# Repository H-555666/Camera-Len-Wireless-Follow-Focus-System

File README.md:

# Camera-Len-Wireless-Follow-Focus-System
***Many documents are not yet complete, the initial version has been released, please wait🌛***

**[简体中文](https://github.com/ZhongWwwHhh/Camera-Len-Wireless-Follow-Focus-System/blob/main/README_ZH_CN.md)**

## Brief Instructions for Use
If you are an enthusiast and only want to make and use it personally, check this document: [Brief instructions for use](https://github.com/ZhongWwwHhh/Camera-Len-Wireless-Follow-Focus-System/blob/main/Documentation/Quickstart.md)

## Developer
This project always welcomes your guidance and help!!!  
This project was designed exclusively for Raspberry Pi Pico.
If you want to use it on other micropython-capable microcontrollers(such as a more powerful Arduino or pyboard), there's another [code explanation](https://github.com/ZhongWwwHhh/Camera-Len-Wireless-Follow-Focus-System/blob/main/Documentation/Codeinterpretation.md) will make this process easier

## Introduction to Project
The project currently implements a rocker potentiometer (the one on an aeromodelling remote control) to remotely and wirelessly control a stepper motor.  
It only requires two Raspberry Pi Pico, a ULN2003 and its driven stepper motor, and a pair of wireless transceiver modules, aiming to achieve the same functional equipment as an expensive commercial wireless follower.  
***In the future, it will gradually increase to be able to control the version of three motors, and add more powerful functions such as A-B point limit, see [Development Log](https://github.com/ZhongWwwHhh/Camera-Len-Wireless-Follow-Focus-System/blob/main/Documentation/Updatelog.md)***  
Receiver and transmitter use the same modular hardware design (PCB), Transmitter-receiver conversion can be achieved by simply brushing different programs  
All software will use micropython for easy modification and application, and all hardware will be designed with Kicad

## Development and business use
Please note: **All software and hardware in this repository follow GPL3. 0 (GNU General Public License v3.0)**  
You can **get usage modifications**, but everything will continue to follow GPL3. 0 Protocol  
If you make it a commodity, then you **have to** let **anyone** know **its nature and get the source code / source design file**  
See for more information [original GPL3.0 file](https://github.com/ZhongWwwHhh/Camera-Len-Wireless-Follow-Focus-System/blob/main/LICENSE)

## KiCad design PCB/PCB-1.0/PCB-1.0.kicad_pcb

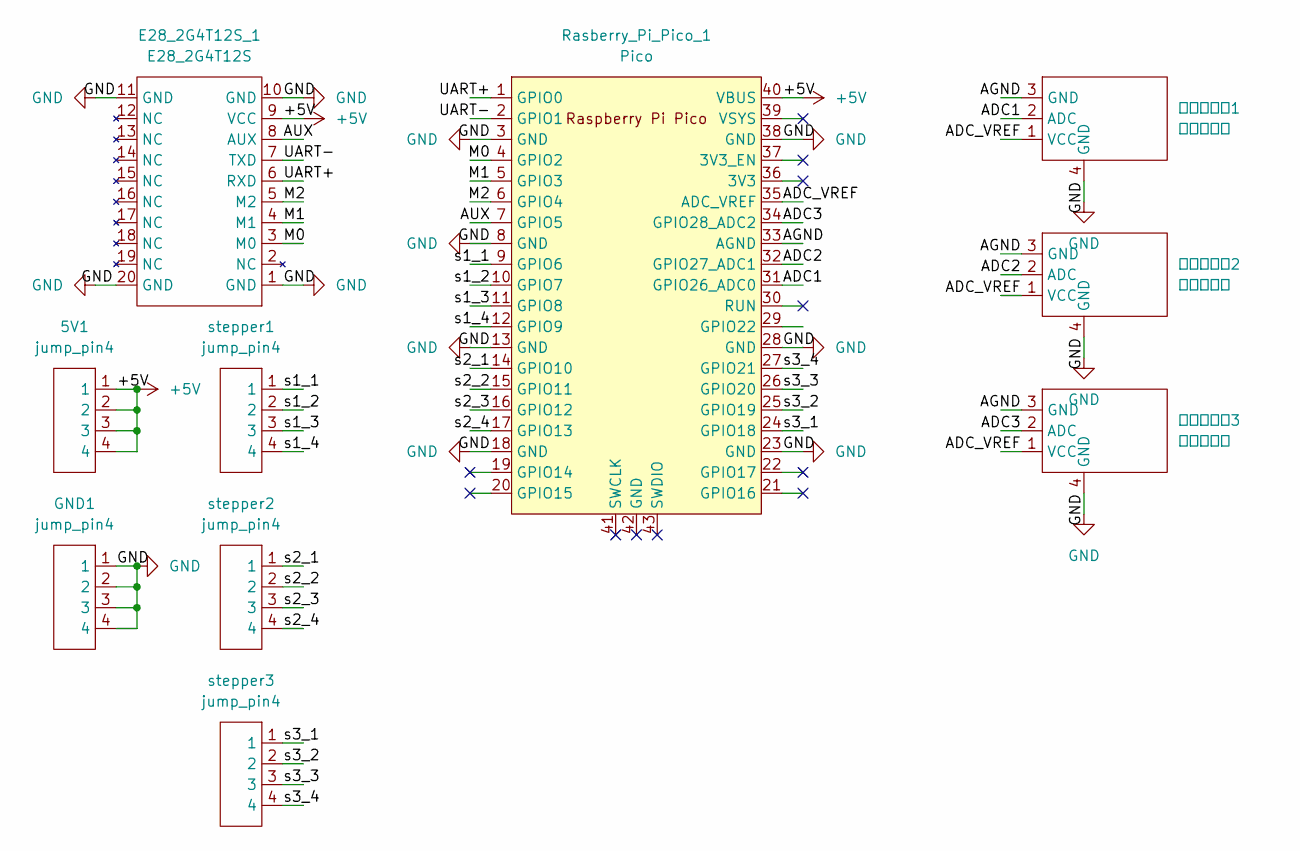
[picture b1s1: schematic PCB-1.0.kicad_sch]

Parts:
5V1: jump_pin4; SIP-4
E28_2G4T12S_1: E28_2G4T12S
GND1: jump_pin4; SIP-4
Rasberry_Pi_Pico_1: Pico; RPi_Pico_SMD_TH
stepper1, stepper2, stepper3: jump_pin4; SIP-4
摇杆电位器1, 摇杆电位器2, 摇杆电位器3: 摇杆电位器

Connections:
+5V: 5V1.1, 5V1.2, 5V1.3, 5V1.4, E28_2G4T12S_1.9 (VCC), Rasberry_Pi_Pico_1.40 (VBUS)
/ADC1: Rasberry_Pi_Pico_1.31 (GPIO26_ADC0), 摇杆电位器1.2 (ADC)
/ADC2: Rasberry_Pi_Pico_1.32 (GPIO27_ADC1), 摇杆电位器2.2 (ADC)
/ADC3: Rasberry_Pi_Pico_1.34 (GPIO28_ADC2), 摇杆电位器3.2 (ADC)
/ADC_VREF: Rasberry_Pi_Pico_1.35 (ADC_VREF), 摇杆电位器1.1 (VCC), 摇杆电位器2.1 (VCC), 摇杆电位器3.1 (VCC)
/AGND: Rasberry_Pi_Pico_1.33 (AGND), 摇杆电位器1.3 (GND), 摇杆电位器2.3 (GND), 摇杆电位器3.3 (GND)
/AUX: E28_2G4T12S_1.8 (AUX), Rasberry_Pi_Pico_1.7 (GPIO5)
/M0: E28_2G4T12S_1.3 (M0), Rasberry_Pi_Pico_1.4 (GPIO2)
/M1: E28_2G4T12S_1.4 (M1), Rasberry_Pi_Pico_1.5 (GPIO3)
/M2: E28_2G4T12S_1.5 (M2), Rasberry_Pi_Pico_1.6 (GPIO4)
/UART+: E28_2G4T12S_1.6 (RXD), Rasberry_Pi_Pico_1.1 (GPIO0)
/UART-: E28_2G4T12S_1.7 (TXD), Rasberry_Pi_Pico_1.2 (GPIO1)
/s1_1: Rasberry_Pi_Pico_1.9 (GPIO6), stepper1.1
/s1_2: Rasberry_Pi_Pico_1.10 (GPIO7), stepper1.2
/s1_3: Rasberry_Pi_Pico_1.11 (GPIO8), stepper1.3
/s1_4: Rasberry_Pi_Pico_1.12 (GPIO9), stepper1.4
/s2_1: Rasberry_Pi_Pico_1.14 (GPIO10), stepper2.1
/s2_2: Rasberry_Pi_Pico_1.15 (GPIO11), stepper2.2
/s2_3: Rasberry_Pi_Pico_1.16 (GPIO12), stepper2.3
/s2_4: Rasberry_Pi_Pico_1.17 (GPIO13), stepper2.4
/s3_1: Rasberry_Pi_Pico_1.24 (GPIO18), stepper3.1
/s3_2: Rasberry_Pi_Pico_1.25 (GPIO19), stepper3.2
/s3_3: Rasberry_Pi_Pico_1.26 (GPIO20), stepper3.3
/s3_4: Rasberry_Pi_Pico_1.27 (GPIO21), stepper3.4
GND: E28_2G4T12S_1.1 (GND), E28_2G4T12S_1.10 (GND), E28_2G4T12S_1.11 (GND), E28_2G4T12S_1.20 (GND), GND1.1, GND1.2, GND1.3, GND1.4, Rasberry_Pi_Pico_1.3 (GND), Rasberry_Pi_Pico_1.8 (GND), Rasberry_Pi_Pico_1.13 (GND), Rasberry_Pi_Pico_1.18 (GND), Rasberry_Pi_Pico_1.23 (GND), Rasberry_Pi_Pico_1.28 (GND), Rasberry_Pi_Pico_1.38 (GND), 摇杆电位器1.4 (GND), 摇杆电位器2.4 (GND), 摇杆电位器3.4 (GND)

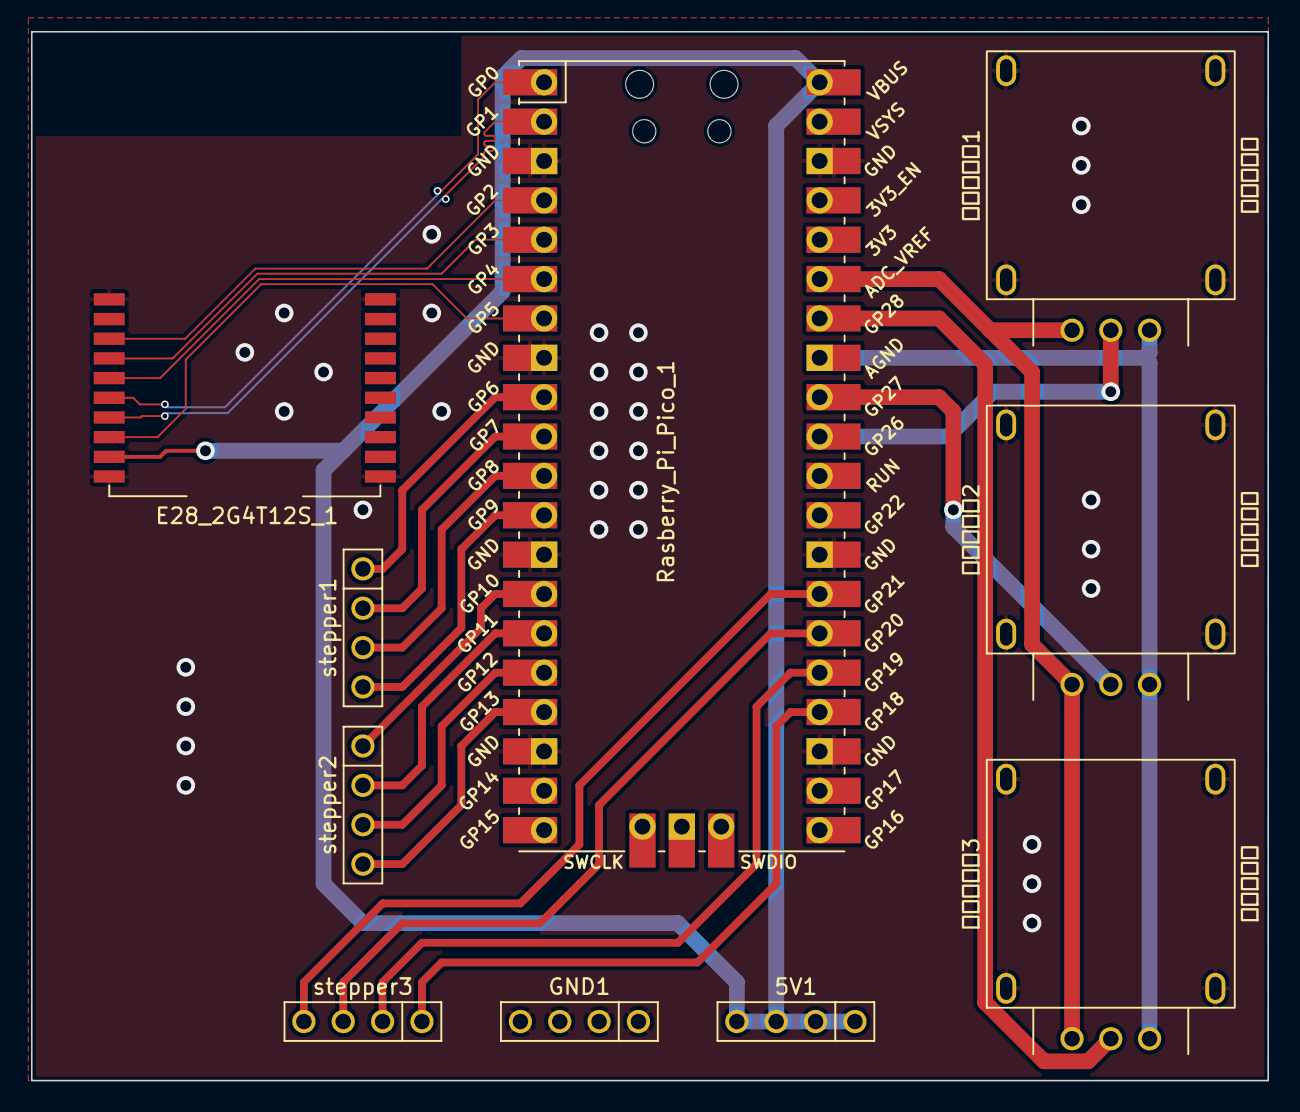
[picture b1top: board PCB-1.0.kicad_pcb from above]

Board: 2 copper layers, 79.8 x 67.7 mm, 10 parts (0 on the bottom side), 25 nets.

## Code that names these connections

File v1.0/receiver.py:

from machine import Pin, UART
import time, _thread

# set GPIO for stepper
s1_1 = Pin(6,Pin.OUT)
s1_2 = Pin(7,Pin.OUT)
s1_3 = Pin(8,Pin.OUT)
s1_4 = Pin(9,Pin.OUT)

# set GPIO for led
led = Pin(25,Pin.OUT)
led.high() # if led light, it is not in working

# set GPIO for E28
uart = UART(0, 9600, bits=8, tx=Pin(0), rx=Pin(1), parity=None, stop=1)
m0 = Pin(2,Pin.OUT)
m1 = Pin(3,Pin.OUT)
m2 = Pin(4,Pin.OUT)
aux = Pin(5,Pin.IN,Pin.PULL_UP)

# wait starting of E28
def E28_start():
    m0.value(0)
    m1.value(0)
    m2.value(1)
    while aux.value() == 0:
        time.sleep_ms(300)
    led.low() # it is  able to work

# led flashing
def led_flash(c, t):
    for x in range(c):
        led.high()
        time.sleep_ms(t)
        led.low()
        time.sleep_ms(t)

# config E28
E28_start()
m0.value(1)
m1.value(1)
m2.value(1)
led.high() # it means that E28 is just configing
time.sleep_ms(500)
uart.write(b"\xc0\x57\x57\x13\x5d\x04") # set the original config to E28
time.sleep_ms(500)
uart.read() # clean the message from uart
E28_start() # now it can work

# control of stepper
def step():
    while True:
        d=direction
        dd=delay
        if d == 0:
            s1_1(0)
            s1_2(0)
            s1_3(0)
            s1_4(0)
            time.sleep_ms(100)
        elif d == 1:
        
            s1_1(0)
            s1_2(0)
            s1_3(0)
            s1_4(1)
            time.sleep_ms(dd)
            
            s1_1(0)
            s1_2(0)
            s1_3(1)
            s1_4(1)
            time.sleep_ms(dd)
            
            s1_1(0)
            s1_2(0)
            s1_3(1)
            s1_4(0)
            time.sleep_ms(dd)
            
            s1_1(0)
            s1_2(1)
            s1_3(1)
            s1_4(0)
            time.sleep_ms(dd)
            
            s1_1(0)
            s1_2(1)
            s1_3(0)
            s1_4(0)
            time.sleep_ms(dd)
            
            s1_1(1)
            s1_2(1)
            s1_3(0)
            s1_4(0)
            time.sleep_ms(dd)
            
            s1_1(1)
            s1_2(0)
            s1_3(0)
            s1_4(0)
            time.sleep_ms(dd)
            
            s1_1(1)
            s1_2(0)
            s1_3(0)
            s1_4(1)
            time.sleep_ms(dd)
        else:
            s1_1(1)
            s1_2(0)
            s1_3(0)
            s1_4(1)
            time.sleep_ms(dd)
            
            s1_1(1)
            s1_2(0)
            s1_3(0)
            s1_4(0)
            time.sleep_ms(dd)
            
            s1_1(1)
            s1_2(1)
            s1_3(0)
            s1_4(0)
            time.sleep_ms(dd)
            
            s1_1(0)
            s1_2(1)
            s1_3(0)
            s1_4(0)
            time.sleep_ms(dd)
            
            s1_1(0)
            s1_2(1)
            s1_3(1)
            s1_4(0)
            time.sleep_ms(dd)
            
            s1_1(0)
            s1_2(0)
            s1_3(1)
            s1_4(0)
            time.sleep_ms(dd)
            
            s1_1(0)
            s1_2(0)
            s1_3(1)
            s1_4(1)
            time.sleep_ms(dd)
            
            s1_1(0)
            s1_2(0)
            s1_3(0)
            s1_4(1)
            time.sleep_ms(dd)

# set an original number for delay and direction
delay = 0
direction = 0

# start the control of stepper
_thread.start_new_thread(step,())

# this is a test
#uart.write('(5,1)')

while True:
    if uart.any()>=1:
        time.sleep_ms(30)
        receive = str(uart.read())
        e = receive.rfind(")")
        s = receive.rfind(",", 0, e)
        direction = int(receive[(s+1):e])
        e = receive.rfind("(", 0, s)
        delay = int(receive[(e+1):s])
    else:
        time.sleep_ms(30)

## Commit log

2022-02-12 Update README.md
    README 1.0
2022-02-12 Create 1,0
    update1.0
2022-02-12 Create main
2022-02-12 Create Quickstart.md
    a document for user
2022-02-12 Create Codeinterpretation.md
    a document for developer
2022-02-15 Rename README.md to README_ZH_CN.md
2022-02-15 Made README in English
